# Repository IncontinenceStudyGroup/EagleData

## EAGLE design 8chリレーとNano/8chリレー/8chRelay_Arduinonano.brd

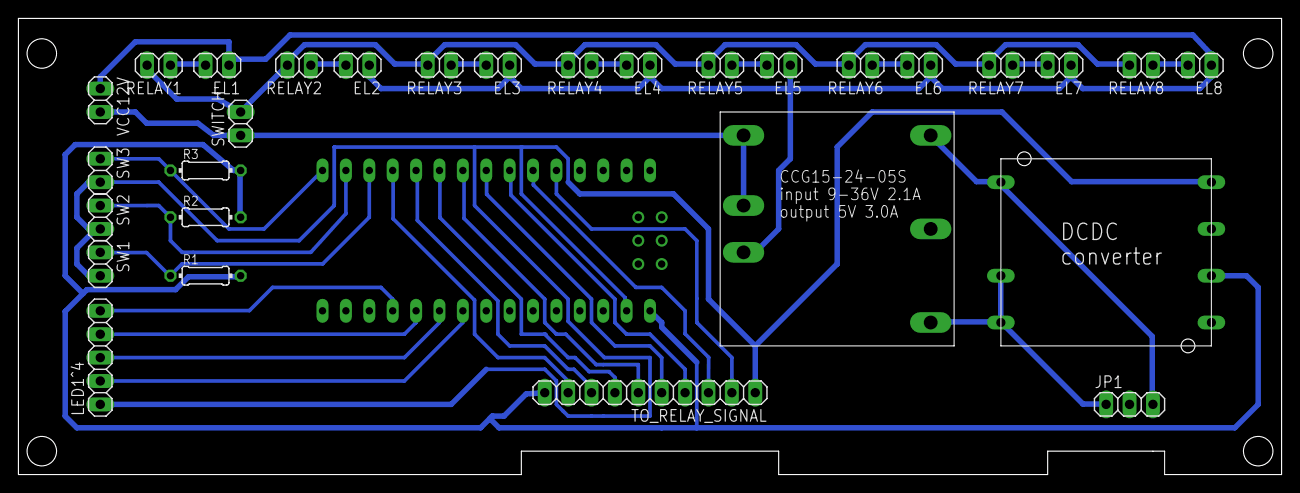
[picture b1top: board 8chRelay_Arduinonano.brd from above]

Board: 2 copper layers, 137.2 x 49.5 mm, 30 parts (0 on the bottom side), 30 nets.

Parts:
DC-DC1: DC-DC-CONVERTER; DC_DC_CONVERTER
EL1, EL2, EL3, EL4, EL5, EL6, EL7, EL8: 1X02
JP1: 1X03
LED1^4: 1X05
R1, R2, R3: 10k; 0204/7
RELAY1, RELAY2, RELAY3, RELAY4, RELAY5, RELAY6, RELAY7, RELAY8: 1X02
SW1, SW2, SW3: 1X02
SWITCH: 1X02
TO_RELAY_SIGNAL: 1X10
U$1: NANO
U$2: CCG15-24-05S
VCC12V: 1X02

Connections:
unnamed: RELAY1.2, RELAY2.2, RELAY3.2, RELAY4.2, RELAY5.2, RELAY6.2, RELAY7.2, RELAY8.2, SWITCH.2
unnamed: EL1.2, RELAY1.1
unnamed: EL2.2, RELAY2.1
unnamed: EL3.2, RELAY3.1
unnamed: EL4.2, RELAY4.1
unnamed: EL5.2, RELAY5.1
unnamed: EL6.2, RELAY6.1
unnamed: EL7.2, RELAY7.1
unnamed: EL8.2, RELAY8.1
unnamed: EL1.1, EL2.1, EL3.1, EL4.1, EL5.1, EL6.1, EL7.1, EL8.1, U$2.+VIN, VCC12V.1
unnamed: DC-DC1.-VIN, DC-DC1.RC, JP1.1, U$2.-VOUT
unnamed: SWITCH.1, U$2.-VIN, U$2.RC, VCC12V.2
unnamed: TO_RELAY_SIGNAL.2, U$1.D2
unnamed: TO_RELAY_SIGNAL.3, U$1.D3
unnamed: TO_RELAY_SIGNAL.4, U$1.D4
unnamed: TO_RELAY_SIGNAL.5, U$1.D5
unnamed: TO_RELAY_SIGNAL.6, U$1.D6
unnamed: TO_RELAY_SIGNAL.7, U$1.D7
unnamed: TO_RELAY_SIGNAL.8, U$1.D8
unnamed: TO_RELAY_SIGNAL.9, U$1.D9
unnamed: R3.1, SW3.1, U$1.D12
unnamed: R2.1, SW2.1, U$1.D11
unnamed: R1.1, SW1.1, U$1.D10
unnamed: LED1^4.5, U$1.A0
unnamed: LED1^4.4, U$1.A1
unnamed: LED1^4.3, U$1.A2
unnamed: LED1^4.2, U$1.A3
unnamed: DC-DC1.+VOUT, LED1^4.1, SW1.2, SW2.2, SW3.2, TO_RELAY_SIGNAL.1, U$1.GND
unnamed: DC-DC1.-VOUT, R1.2, R2.2, R3.2, TO_RELAY_SIGNAL.10, U$1.RAW
unnamed: DC-DC1.+VIN, JP1.3, U$2.+VOUT
